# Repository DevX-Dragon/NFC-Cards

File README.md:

# NFC Cards
So, I’ve been messing around with NFC tech lately. This repo is basically the home for my NFC business card project. I wanted to make something cooler than a piece of paper, so I designed a custom PCB that doubles as a digital business card using the NT3H1101 chip.

## Layouts

## Specifications

- **IC** - NT3H1101
- **Frequency** - 13.56 MHz

## How to make your own

- Clone the repository (or download the kicad folder). Open it. Modify the silkscreen to your likings. I used Canva. Then export gerber files. And Get it manufactured (JLCPCB.PCBWAY,etc)
- Dont forget to post yours online!

## Bill of Material
| Name | Quanity | Links |
| --- | --- | --- | 
| NT3H1101 | x1 | [LCSC](https://www.lcsc.com/product-image/C73156.html) |
| 220nF Capacitor (SMD) |  X1 | [LCSC](https://www.lcsc.com/product-detail/C107186.html) | 
| A SMD LED | x1 | [LCSC](https://www.lcsc.com/product-detail/C965799.html) | 
| 47 ohms ressistor SMD | x1 | [LCSC](https://www.lcsc.com/product-detail/C25118.html) |

**OR**
You can buy x2 fully assembled NFC cards for **USD $38.00** on JLC PCB

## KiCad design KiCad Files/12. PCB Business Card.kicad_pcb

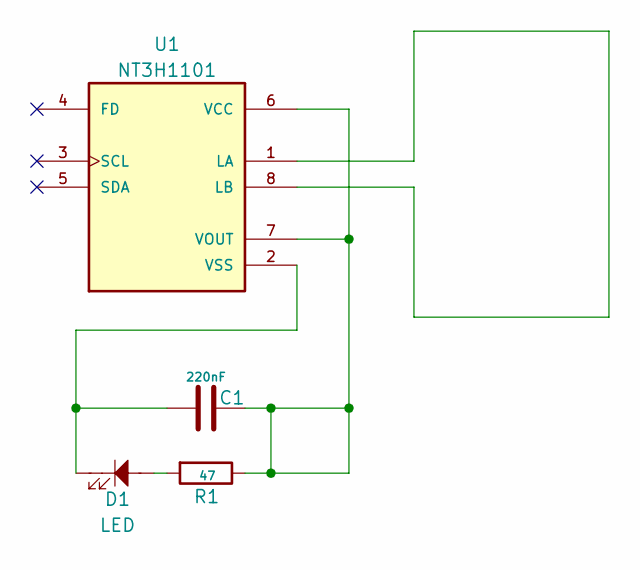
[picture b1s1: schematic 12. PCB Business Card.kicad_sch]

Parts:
C1: 220nF; C_0402_1005Metric
D1: LED; D_0805_2012Metric
R1: 47; C_0402_1005Metric; MFG_PART_NUMBER RC0402FR-0747RL; LCSC C137973
U1: NT3H1101; QFN8P50_160X160X50L40X20N; MFG_PART_NUMBER NT3H2111W0 FHKH; LCSC C73156

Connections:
unnamed: D1.2, R1.2
unnamed: U1.1 (LA), U1.8 (LB)
unnamed: C1.2, R1.1, U1.6 (VCC), U1.7 (VOUT)
unnamed: C1.1, D1.1, U1.2 (VSS)

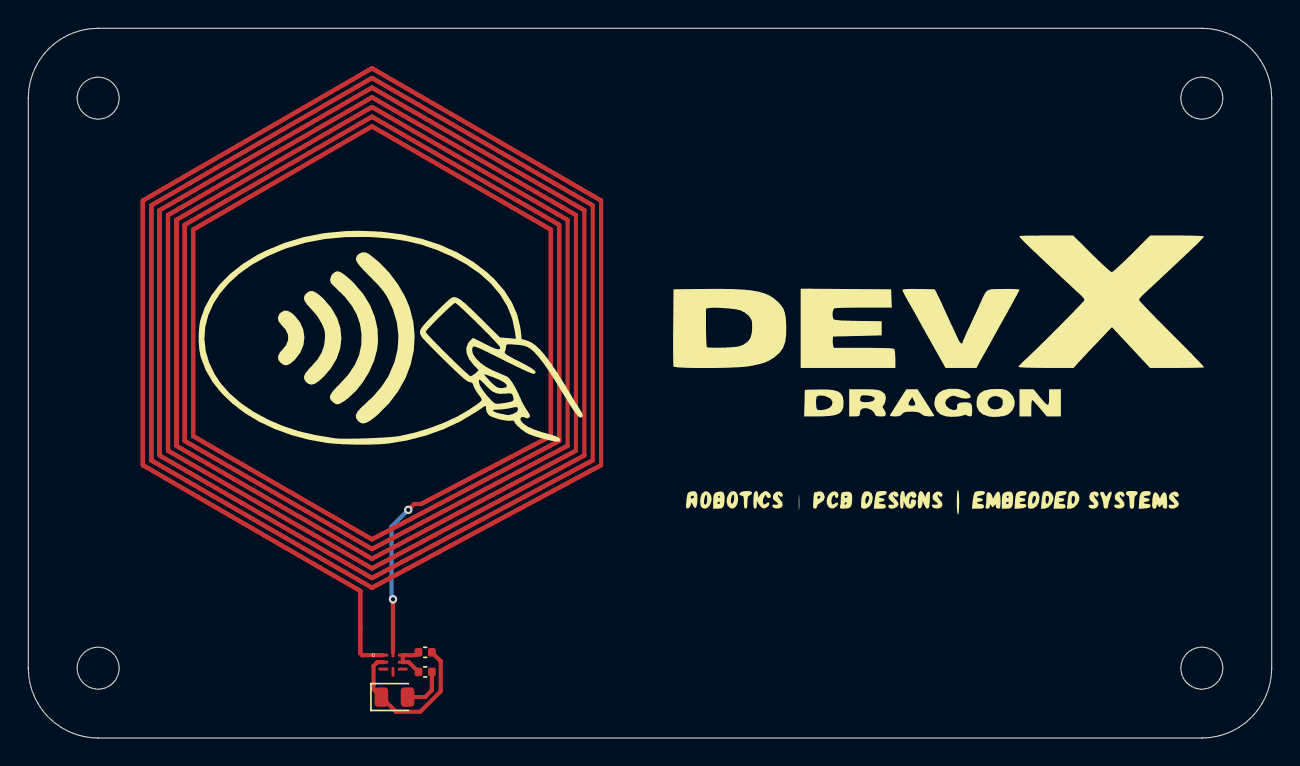
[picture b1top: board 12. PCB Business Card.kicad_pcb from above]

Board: 2 copper layers, 89.0 x 50.8 mm, 4 parts (0 on the bottom side), 4 nets.

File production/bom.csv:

Designator,Footprint,Quantity,Value,LCSC Part #
C1,0402,1,220nF,
D1,0805,1,LED,
R1,0402,1,47,C137973
U1,QFN8P50_160X160X50L40X20N,1,NT3H1101,C73156

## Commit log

2026-03-12 first upload
2026-03-12 KiCad Files
2026-03-12 Adding gerbers
2026-03-14 bom add
